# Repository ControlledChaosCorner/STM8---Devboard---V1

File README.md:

This Board uses an ST STM8S005K6T6C

Component List:

1 × 1 µF capacitor (0805)

4 × 18 pF capacitors (0603)

2 × LEDs (0603)

1 × 4-pin header (2.54 mm, vertical)

1 × USB-C receptacle (6-pin, horizontal)

2 × 14-pin headers (2×7, 2.54 mm, vertical)

1 × 4.7 kΩ resistor (1206)

2 × 499 Ω resistors (1206)

1 × Reset push button (SMD, SPST)

1 × STM8S005K6T6C microcontroller (LQFP-32, 7×7 mm)

1 × 12 MHz crystal (HC49 SMD)

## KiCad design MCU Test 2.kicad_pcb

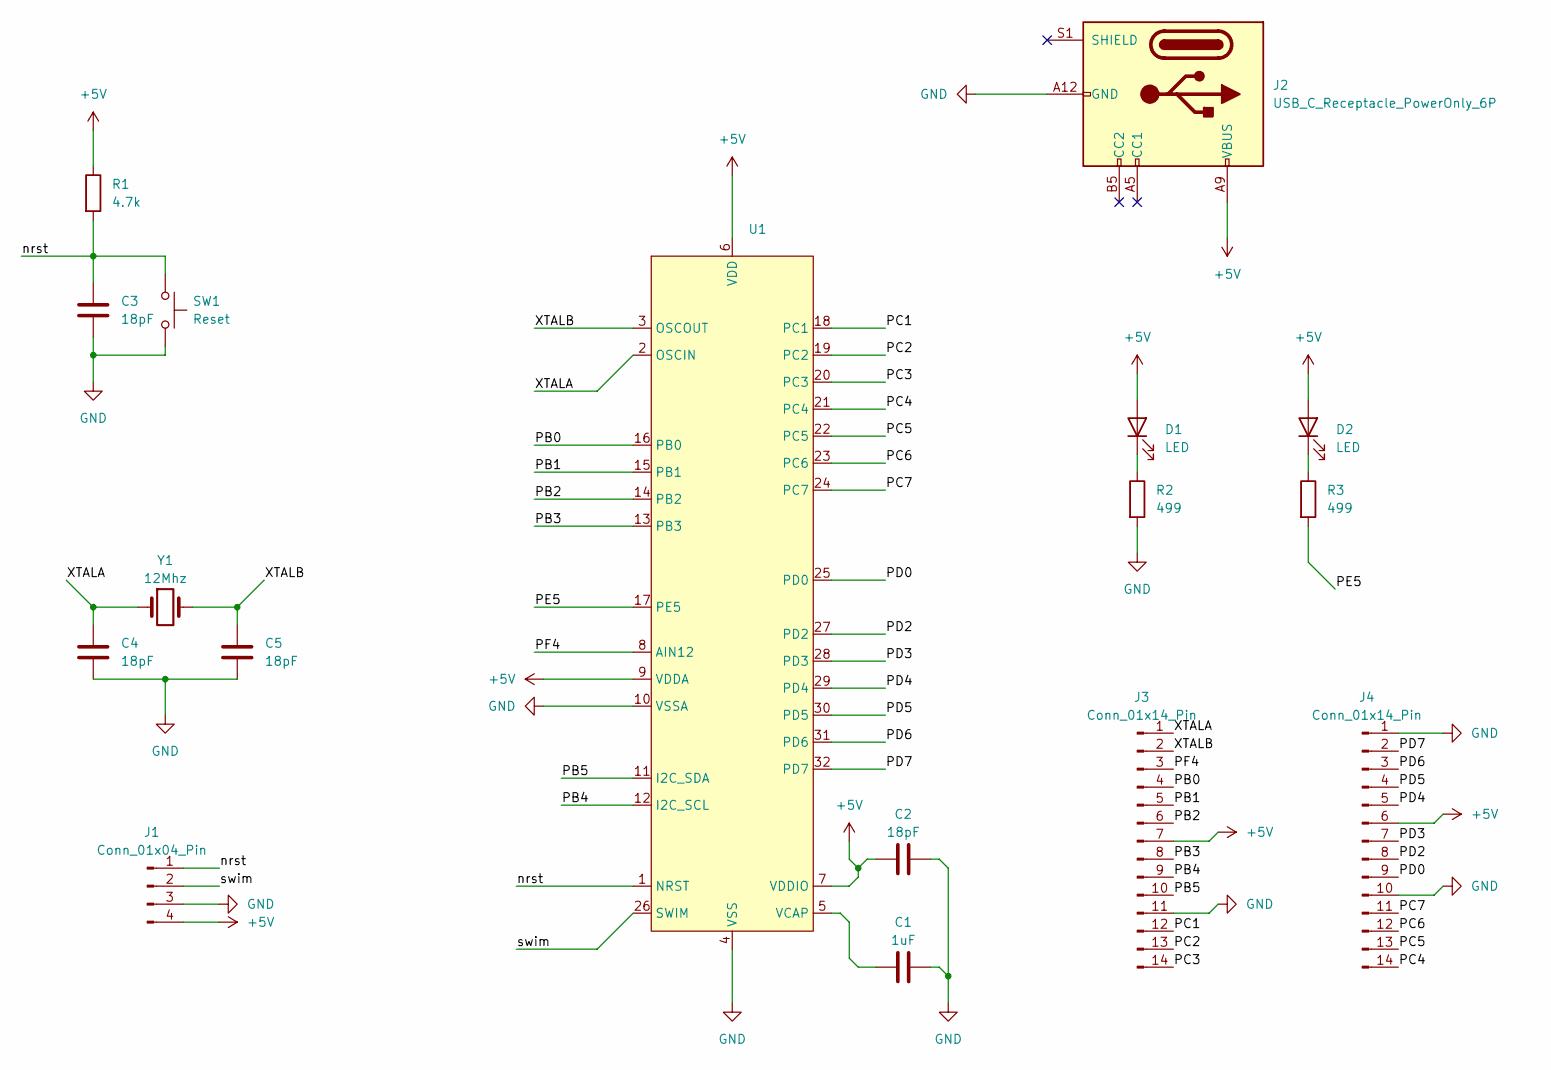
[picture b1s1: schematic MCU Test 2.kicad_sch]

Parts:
C1: 1uF; C_0805_2012Metric
C2, C3, C4, C5: 18pF; C_0603_1608Metric
D1, D2: LED; LED_0603_1608Metric
J1: Conn_01x04_Pin; PinHeader_1x04_P2.54mm_Vertical
J2: USB_C_Receptacle_PowerOnly_6P; USB_C_Receptacle_GCT_USB4125-xx-x_6P_TopMnt_Horizontal
J3, J4: Conn_01x14_Pin; PinHeader_2x07_P2.54mm_Vertical
R1: 4.7k; R_1206_3216Metric
R2, R3: 499; R_1206_3216Metric
SW1: Reset; SW_SPST_CK_RS282G05A3
U1: LQFP-32_7x7mm_P0.8mm
Y1: 12Mhz; Crystal_SMD_HC49-SD_HandSoldering

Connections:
+5V: C2.1, D1.2 (A), D2.2 (A), J1.4, J2.A9 (VBUS), J2.B9 (VBUS), J3.7, J4.6, R1.1, U1.6 (VDD), U1.7 (VDDIO), U1.9 (VDDA)
/PB0: J3.4, U1.16 (PB0)
/PB1: J3.5, U1.15 (PB1)
/PB2: J3.6, U1.14 (PB2)
/PB3: J3.8, U1.13 (PB3)
/PB4: J3.9, U1.12 (I2C_SCL)
/PB5: J3.10, U1.11 (I2C_SDA)
/PC1: J3.12, U1.18 (PC1)
/PC2: J3.13, U1.19 (PC2)
/PC3: J3.14, U1.20 (PC3)
/PC4: J4.14, U1.21 (PC4)
/PC5: J4.13, U1.22 (PC5)
/PC6: J4.12, U1.23 (PC6)
/PC7: J4.11, U1.24 (PC7)
/PD0: J4.9, U1.25 (PD0)
/PD2: J4.8, U1.27 (PD2)
/PD3: J4.7, U1.28 (PD3)
/PD4: J4.5, U1.29 (PD4)
/PD5: J4.4, U1.30 (PD5)
/PD6: J4.3, U1.31 (PD6)
/PD7: J4.2, U1.32 (PD7)
/PE5: R3.2, U1.17 (PE5)
/PF4: J3.3, U1.8 (AIN12)
/XTALA: C4.1, J3.1, U1.2 (OSCIN), Y1.1
/XTALB: C5.1, J3.2, U1.3 (OSCOUT), Y1.2
/nrst: C3.1, J1.1, R1.2, SW1.1, U1.1 (NRST)
/swim: J1.2, U1.26 (SWIM)
GND: C1.2, C2.2, C3.2, C4.2, C5.2, J1.3, J2.A12 (GND), J2.B12 (GND), J3.11, J4.1, J4.10, R2.2, SW1.2, U1.4 (VSS), U1.10 (VSSA)
unnamed: D1.1 (K), R2.1
unnamed: D2.1 (K), R3.1
unnamed: C1.1, U1.5 (VCAP)

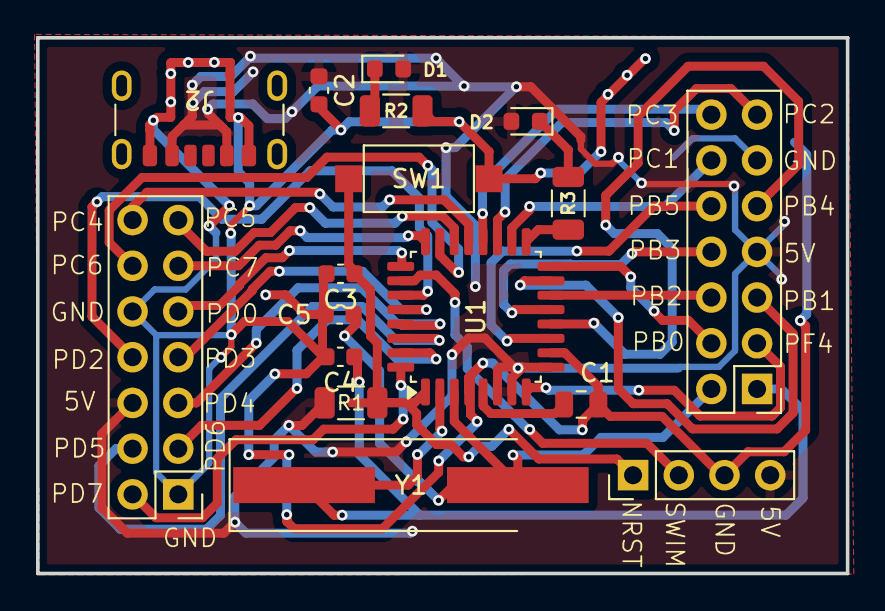
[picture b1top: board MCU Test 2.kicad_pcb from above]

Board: 2 copper layers, 45.0 x 29.8 mm, 17 parts (0 on the bottom side), 31 nets.

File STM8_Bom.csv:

"Reference","Value","Datasheet","Footprint","Qty","DNP"
"C1","1uF","~","Capacitor_SMD:C_0805_2012Metric","1",""
"C2,C3,C4,C5","18pF","~","Capacitor_SMD:C_0603_1608Metric","4",""
"D1,D2","LED","~","LED_SMD:LED_0603_1608Metric","2",""
"J1","Conn_01x04_Pin","~","Connector_PinHeader_2.54mm:PinHeader_1x04_P2.54mm_Vertical","1",""
"J2","USB_C_Receptacle_PowerOnly_6P","https://www.usb.org/sites/default/files/documents/usb_type-c.zip","Connector_USB:USB_C_Receptacle_GCT_USB4125-xx-x_6P_TopMnt_Horizontal","1",""
"J3,J4","Conn_01x14_Pin","~","Connector_PinHeader_2.54mm:PinHeader_2x07_P2.54mm_Vertical","2",""
"R1","4.7k","~","Resistor_SMD:R_1206_3216Metric","1",""
"R2,R3","499","~","Resistor_SMD:R_1206_3216Metric","2",""
"SW1","Reset","~","Button_Switch_SMD:SW_SPST_CK_RS282G05A3","1",""
"U1","~","","Package_QFP:LQFP-32_7x7mm_P0.8mm","1",""
"Y1","12Mhz","~","Crystal:Crystal_SMD_HC49-SD_HandSoldering","1",""
